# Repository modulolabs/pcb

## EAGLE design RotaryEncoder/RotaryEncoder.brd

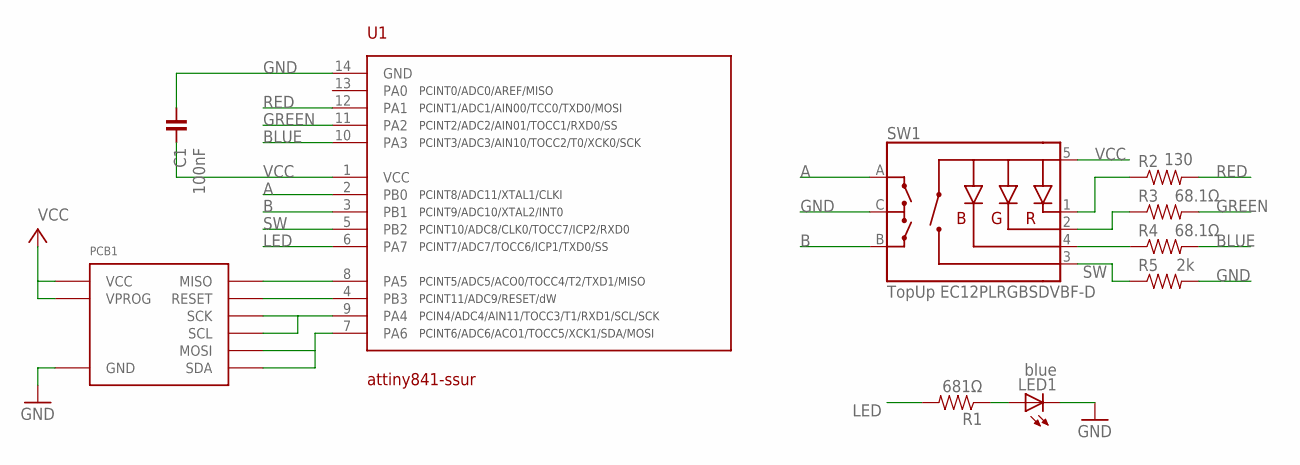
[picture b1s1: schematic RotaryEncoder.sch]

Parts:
C1: 100nF; 0603
LED1: blue; 0805-LED
PCB1: DEVICE-PCB-TABS
R1: 681Ω; 0603
R2: 130; 0603
R3, R4: 68.1Ω; 0603
R5: 2k; 0603
SW1: TopUp EC12PLRGBSDVBF-D; ENCODER_LED_3
U1: attiny841-ssur; SOIC14

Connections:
A: SW1.A, U1.2 (PB0)
B: SW1.B, U1.3 (PB1)
BLUE: R4.2, U1.10 (PA3)
GND: C1.2, LED1.C, PCB1.BUS0 (GND), R5.2, SW1.C, U1.14 (GND)
GREEN: R3.2, U1.11 (PA2)
LED: R1.2, U1.6 (PA7)
MISO: PCB1.PROG3 (MISO), U1.8 (PA5)
unnamed: R2.1, SW1.1 (-R)
unnamed: R3.1, SW1.2 (-G)
unnamed: R4.1, SW1.4 (-B)
unnamed: LED1.A, R1.1
RED: R2.2, U1.12 (PA1)
RESET: PCB1.PROG1 (RESET), U1.4 (PB3)
SCL/SCK: PCB1.BUS3 (SCL), PCB1.PROG2 (SCK), U1.9 (PA4)
SDA/MOSI: PCB1.BUS1 (SDA), PCB1.PROG4 (MOSI), U1.7 (PA6)
SW: R5.1, SW1.3 (SW), U1.5 (PB2)
VCC: C1.1, PCB1.BUS2 (VCC), PCB1.PROG0 (VPROG), SW1.5 (+), U1.1 (VCC)

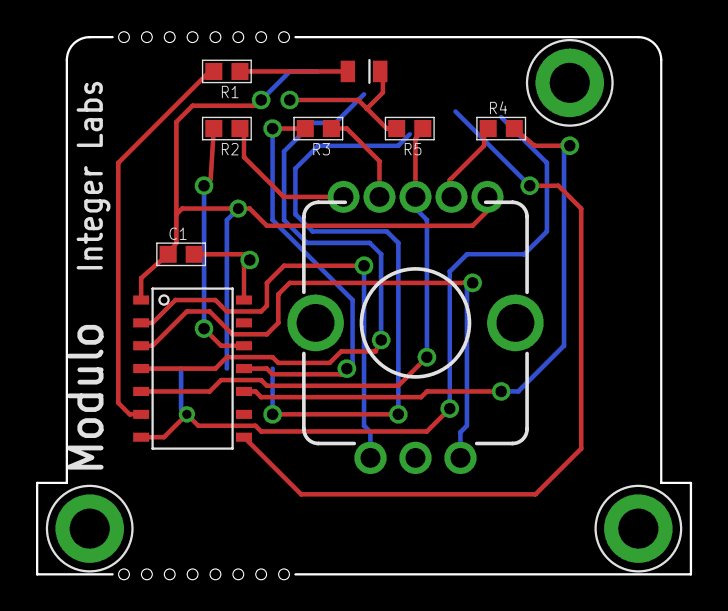
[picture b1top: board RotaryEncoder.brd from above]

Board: 2 copper layers, 10 parts (0 on the bottom side), 17 nets.

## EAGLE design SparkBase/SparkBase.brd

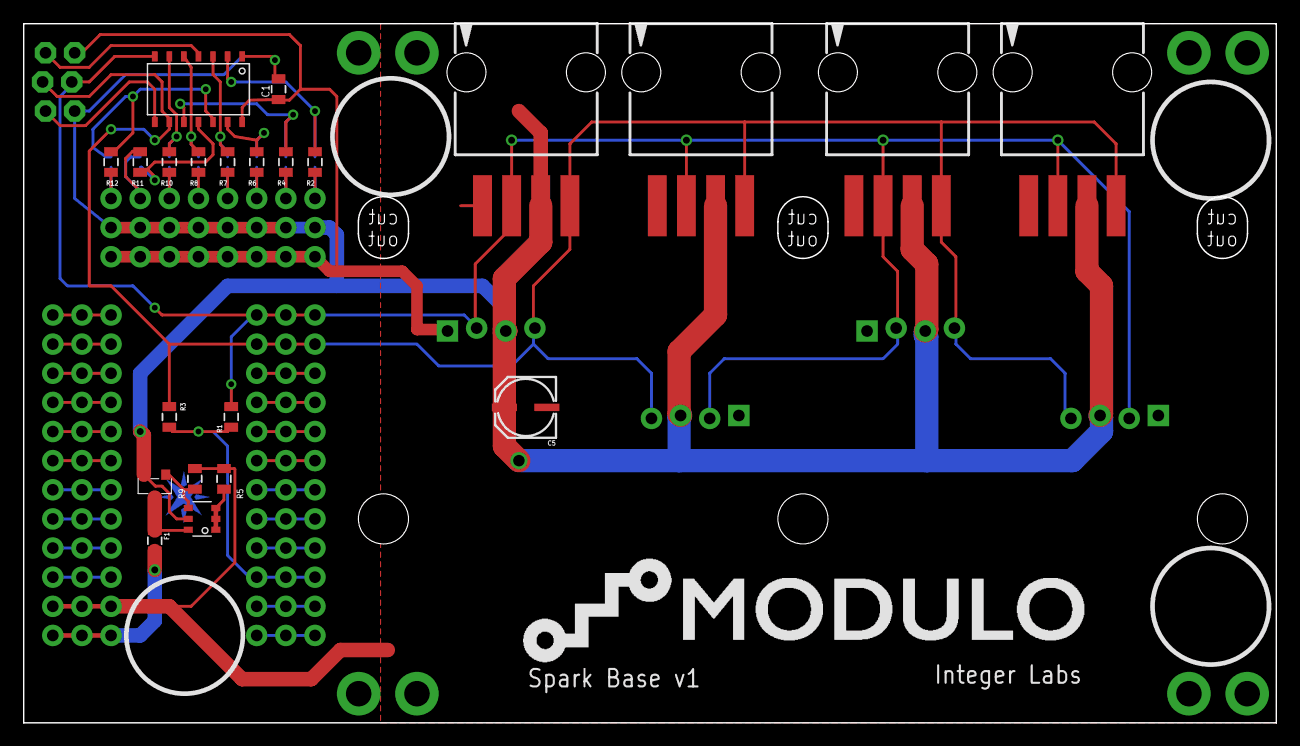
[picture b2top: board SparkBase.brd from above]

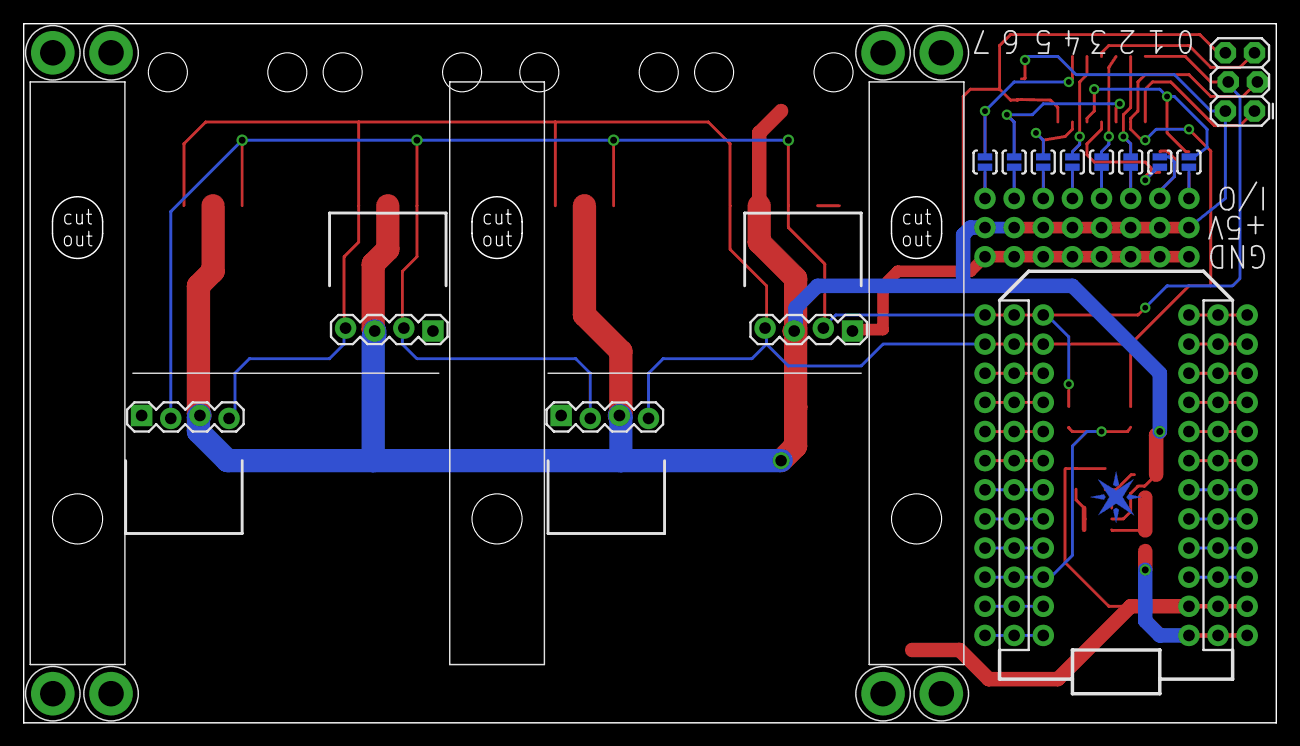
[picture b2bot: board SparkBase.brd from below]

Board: 2 copper layers, 109.2 x 61.0 mm, 52 parts (29 on the bottom side), 46 nets.

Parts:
C1: 0805
C5: PANASONIC_C
F1: 0805
J1: AVR_SPI_PRG_62X3_LOCK; 2X3_LOCK
JP1, JP4, JP11, JP14: 1X04_LOCK
JP2, JP3, JP5: 1X08_NO_SILK
Q2: DMMT5401; SOT-26
Q3: DMG2305UX; MICRO3
R1, R3: 1k; 0805
R2, R4, R6, R7, R8, R10, R11, R12: 130; 0805
R5: 10k 1%; 0805
R9: 47k 1%; 0805
SJ1, SJ2, SJ3, SJ4, SJ5, SJ6, SJ7, SJ8: SOLDERJUMPERNO; SJ_2S-NO
U$1: SPARK_LOGO_PLUS_PLANE
U$2: SPARK_CORE; SPARK_CORE_STACKABLE
U$3, U$4, U$5: CARD-GUIDE-2"
U$6: TINY841; SOIC14
U$7, U$8, U$9, U$10, U$11, U$12, U$13, U$14: HOLE#2; HOLE-#2
U$15: LOGO_WITH_TEXT_0.5
X2, X3, X4, X5: C-GRID-04-15-91; 15-91-04

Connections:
3.3V: R1.1, R3.1, U$2.22, U$2.#22, U$2.@22
GND: C1.1, C5.-, J1.6, JP1.1, JP3.1, JP3.2, JP3.3, JP3.4, JP3.5, JP3.6, JP3.7, JP3.8, JP4.1, JP11.1, JP14.1, R5.1, R9.1, U$2.2, U$2.#2, U$2.@2, U$6.14, X2.1, X3.1, X4.1, X5.1
GPIO0: R12.1, SJ1.2, U$6.12
GPIO1: R11.1, SJ2.2, U$6.11
GPIO2: R10.1, SJ3.2, U$6.6
GPIO3: R8.1, SJ4.2, U$6.5
GPIO4: R7.1, SJ5.2, U$6.3
GPIO5: R6.1, SJ6.2, U$6.13
GPIO6: R4.1, SJ7.2, U$6.10
GPIO7: R2.1, SJ8.2, U$6.2
MISO: J1.1, U$6.8
unnamed: U$2.3, U$2.#3, U$2.@3
unnamed: U$2.4, U$2.#4, U$2.@4
unnamed: U$2.5, U$2.#5, U$2.@5
unnamed: U$2.6, U$2.#6, U$2.@6
unnamed: U$2.7, U$2.#7, U$2.@7
unnamed: U$2.8, U$2.#8, U$2.@8
unnamed: U$2.9, U$2.#9, U$2.@9
unnamed: U$2.10, U$2.#10, U$2.@10
unnamed: U$2.11, U$2.#11, U$2.@11
unnamed: U$2.12, U$2.#12, U$2.@12
unnamed: U$2.24, U$2.#24, U$2.@24
unnamed: U$2.23, U$2.#23, U$2.@23
unnamed: U$2.21, U$2.#21, U$2.@21
unnamed: Q2.1, Q2.2, Q2.3, R5.2
unnamed: U$2.20, U$2.#20, U$2.@20
unnamed: Q2.4, Q3.1, R9.2
unnamed: U$2.19, U$2.#19, U$2.@19
unnamed: U$2.18, U$2.#18, U$2.@18
unnamed: U$2.17, U$2.#17, U$2.@17
unnamed: U$2.16, U$2.#16, U$2.@16
unnamed: U$2.15, U$2.#15, U$2.@15
unnamed: JP5.1, R12.2, SJ1.1
unnamed: JP5.2, R11.2, SJ2.1
unnamed: JP5.3, R10.2, SJ3.1
unnamed: JP5.4, R8.2, SJ4.1
unnamed: JP5.5, R7.2, SJ5.1
unnamed: JP5.6, R6.2, SJ6.1
unnamed: JP5.7, R4.2, SJ7.1
unnamed: JP5.8, R2.2, SJ8.1
RESET: J1.5, U$6.4
SCL: J1.3, JP1.4, JP4.4, JP11.4, JP14.4, R3.2, U$2.14, U$2.#14, U$2.@14, U$6.9, X2.4, X3.4, X4.4, X5.4
SDA: J1.4, JP1.2, JP4.2, JP11.2, JP14.2, R1.2, U$2.13, U$2.#13, U$2.@13, U$6.7, X2.2, X3.2, X4.2, X5.2
VCC: C1.2, C5.+, J1.2, JP1.3, JP2.1, JP2.2, JP2.3, JP2.4, JP2.5, JP2.6, JP2.7, JP2.8, JP4.3, JP11.3, JP14.3, Q2.5, Q3.2, U$6.1, X2.3, X3.3, X4.3, X5.3
VIN: F1.2, U$2.1, U$2.#1, U$2.@1
VREG: F1.1, Q2.6, Q3.3

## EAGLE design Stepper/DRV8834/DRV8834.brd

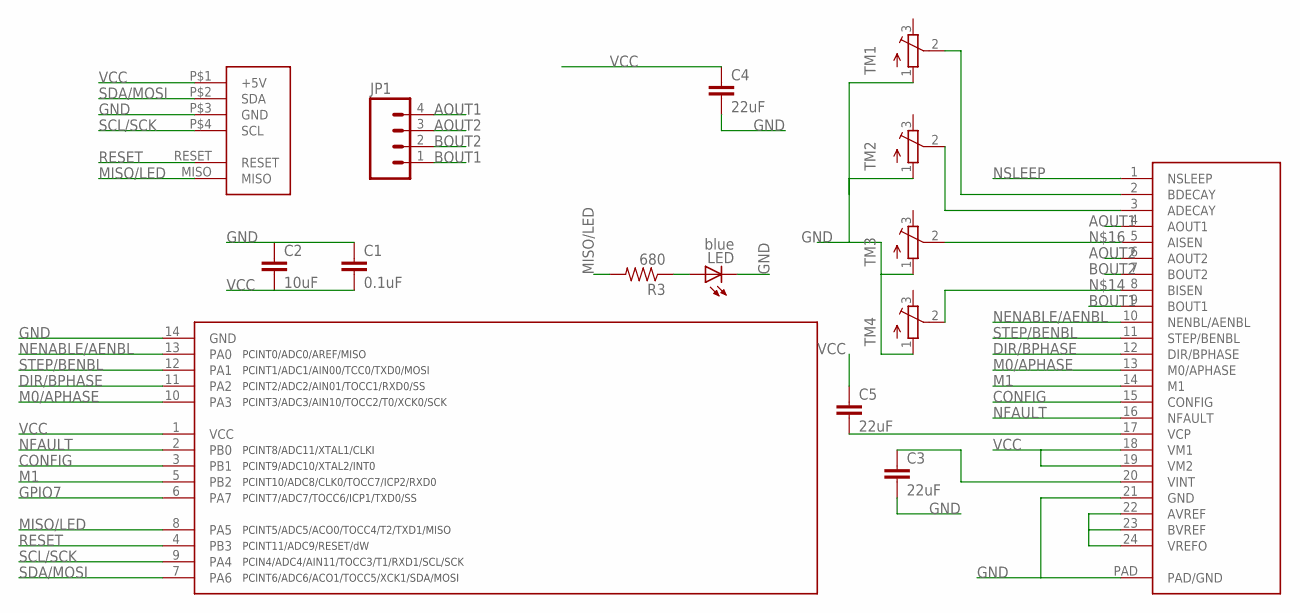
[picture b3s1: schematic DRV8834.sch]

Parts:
C1: 0.1uF; 0805
C2: 10uF; 0805
C3, C4, C5: 22uF; 0805
JP1: M04SCREW_LOCK; SCREWTERMINAL-3.5MM-4_LOCK
LED: blue; CHIPLED_1206
R3: 680; 0805
TM1, TM2, TM3, TM4: TRIMPOTTC33X; TC33X
U$1: DRV8834; HTSSOP-24
U$3: TINY841; SOIC14
U$4: FOOTPRINT

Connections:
AOUT1: JP1.4, U$1.4 (AOUT1)
AOUT2: JP1.3, U$1.6 (AOUT2)
BOUT1: JP1.1, U$1.9 (BOUT1)
BOUT2: JP1.2, U$1.7 (BOUT2)
CONFIG: U$1.15 (CONFIG), U$3.3 (PB1)
DIR/BPHASE: U$1.12 (DIR/BPHASE), U$3.11 (PA2)
GND: C1.1, C2.1, C3.2, C4.2, LED.C, TM1.1 (A), TM2.1 (A), TM3.1 (A), TM4.1 (A), U$1.21 (GND), U$1.PAD (PAD/GND), U$3.14 (GND), U$4.P$3 (GND)
GPIO7: U$3.6 (PA7)
M0/APHASE: U$1.13 (M0/APHASE), U$3.10 (PA3)
M1: U$1.14 (M1), U$3.5 (PB2)
MISO/LED: R3.2, U$3.8 (PA5), U$4.MISO
unnamed: LED.A, R3.1
unnamed: C5.2, U$1.17 (VCP)
unnamed: TM1.2 (S), U$1.2 (BDECAY)
unnamed: TM2.2 (S), U$1.3 (ADECAY)
unnamed: C3.1, U$1.20 (VINT)
unnamed: U$1.22 (AVREF), U$1.23 (BVREF), U$1.24 (VREFO)
unnamed: TM4.2 (S), U$1.8 (BISEN)
unnamed: TM3.2 (S), U$1.5 (AISEN)
NENABLE/AENBL: U$1.10 (NENBL/AENBL), U$3.13 (PA0)
NFAULT: U$1.16 (NFAULT), U$3.2 (PB0)
NSLEEP: U$1.1 (NSLEEP)
RESET: U$3.4 (PB3), U$4.RESET
SCL/SCK: U$3.9 (PA4), U$4.P$4 (SCL)
SDA/MOSI: U$3.7 (PA6), U$4.P$2 (SDA)
STEP/BENBL: U$1.11 (STEP/BENBL), U$3.12 (PA1)
VCC: C1.2, C2.2, C4.1, C5.1, U$1.18 (VM1), U$1.19 (VM2), U$3.1 (VCC), U$4.P$1 (+5V)

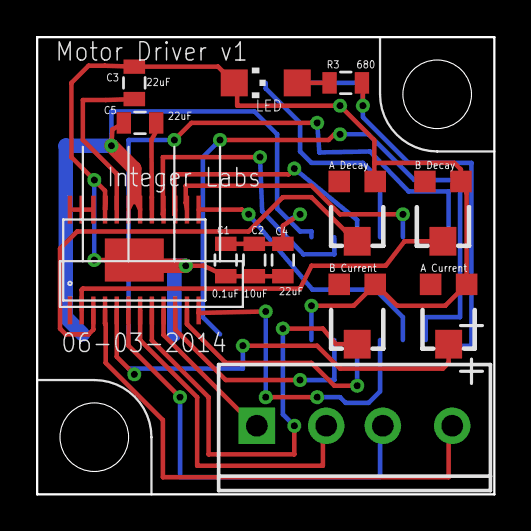
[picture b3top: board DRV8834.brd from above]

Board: 2 copper layers, 25.4 x 25.4 mm, 15 parts (1 on the bottom side), 25 nets.

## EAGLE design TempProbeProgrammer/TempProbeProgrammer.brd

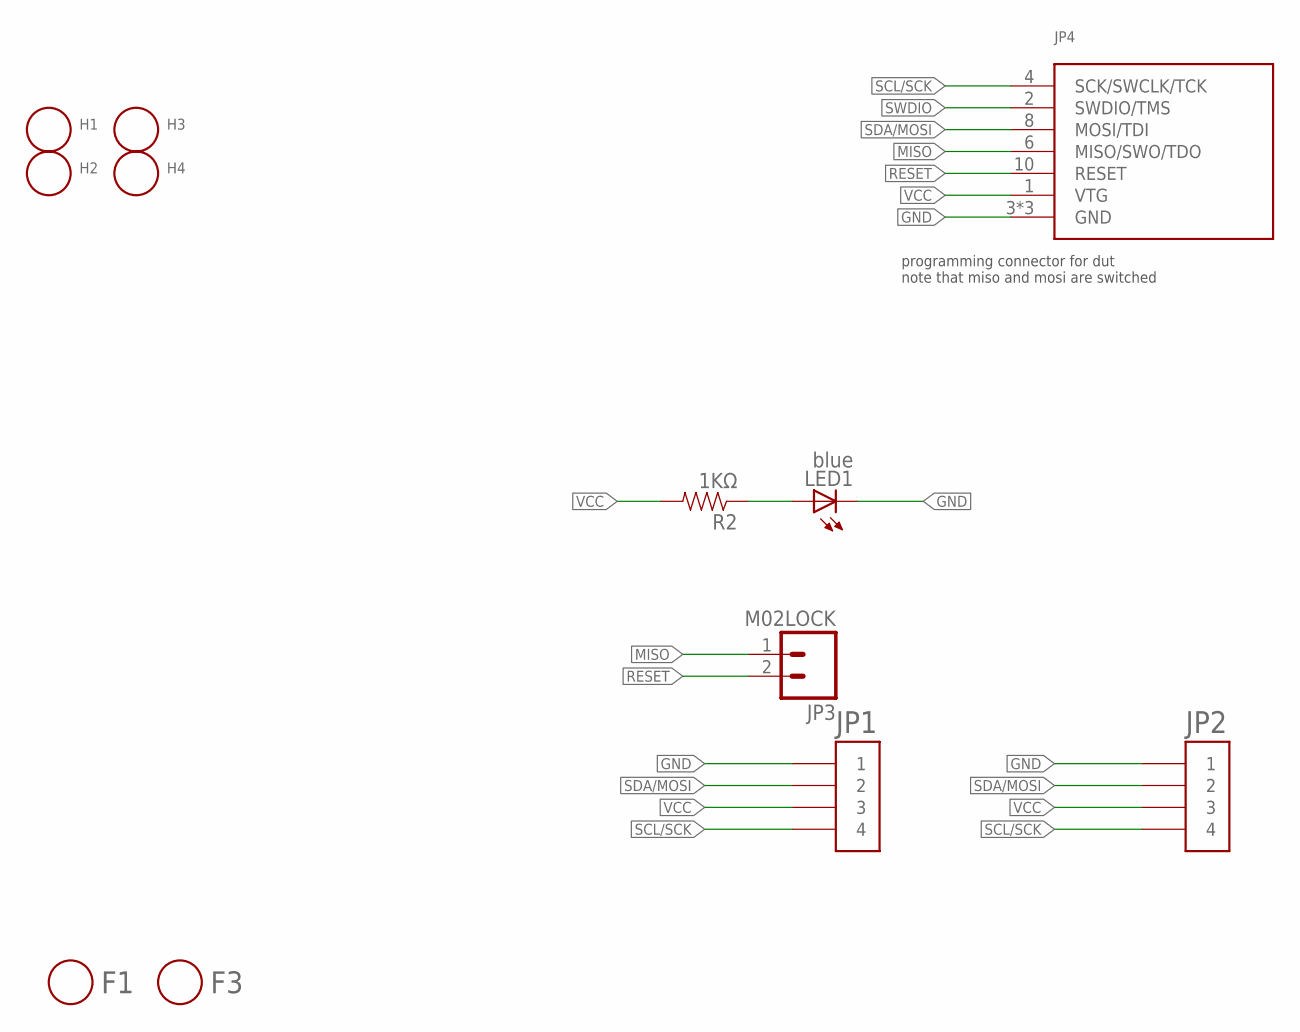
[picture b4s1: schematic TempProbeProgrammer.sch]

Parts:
F1, F3: FIDUCIAL; FIDUCIAL_1MM
H1, H2, H3, H4: HOLE#4; HOLE-#4
JP1, JP2: HEADER-1X4-JST-PA-SIDE-SMD; JST-PA-SIDE-SMD
JP3: M02LOCK; 1X02_LOCK; PARTNUM EXCLUDE
JP4: ICSP; 2X5-.05
LED1: blue; 0805-LED
R2: 1KΩ; 0603

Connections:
GND: JP1.1, JP2.1, JP4.3 (GND), JP4.5 (GND), JP4.9 (GND), LED1.C
MISO: JP3.1, JP4.6 (MISO/SWO/TDO)
unnamed: LED1.A, R2.1
RESET: JP3.2, JP4.10 (RESET)
SCL/SCK: JP1.4, JP2.4, JP4.4 (SCK/SWCLK/TCK)
SDA/MOSI: JP1.2, JP2.2, JP4.8 (MOSI/TDI)
SWDIO: JP4.2 (SWDIO/TMS)
VCC: JP1.3, JP2.3, JP4.1 (VTG), R2.2

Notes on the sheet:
programming connector for dut note that miso and mosi are switched

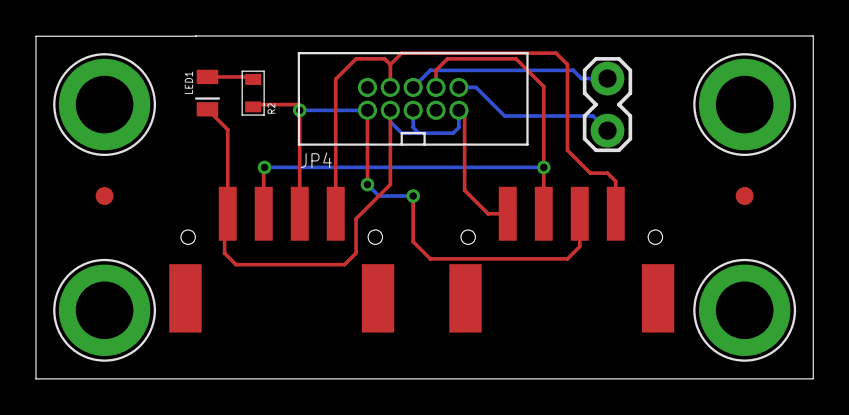
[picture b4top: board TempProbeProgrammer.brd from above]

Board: 2 copper layers, 43.2 x 19.1 mm, 12 parts (0 on the bottom side), 7 nets.

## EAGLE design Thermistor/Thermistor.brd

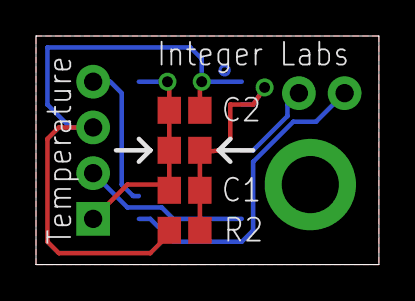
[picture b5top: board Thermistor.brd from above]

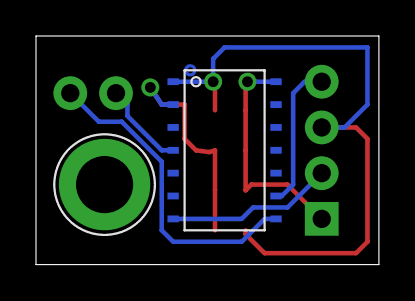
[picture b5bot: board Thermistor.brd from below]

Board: 2 copper layers, 19.1 x 12.7 mm, 8 parts (2 on the bottom side), 7 nets.

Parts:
C1, C2: C0805
JP2: 1X04_NO_SILK
JP4: M021X02_NO_SILK; 1X02_NO_SILK
R1, R2: R0805
U$1: TINY841; SOIC14
U$2: HOLE#4; HOLE-#4

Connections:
GND: C1.1, C2.1, JP2.1, R1.2, U$1.14
MISO: JP4.2, U$1.8
unnamed: C1.2, R1.1, R2.2, U$1.2
RESET: JP4.1, U$1.4
SCL: JP2.4, U$1.9
SDA: JP2.2, U$1.7
VCC: C2.2, JP2.3, R2.1, U$1.1

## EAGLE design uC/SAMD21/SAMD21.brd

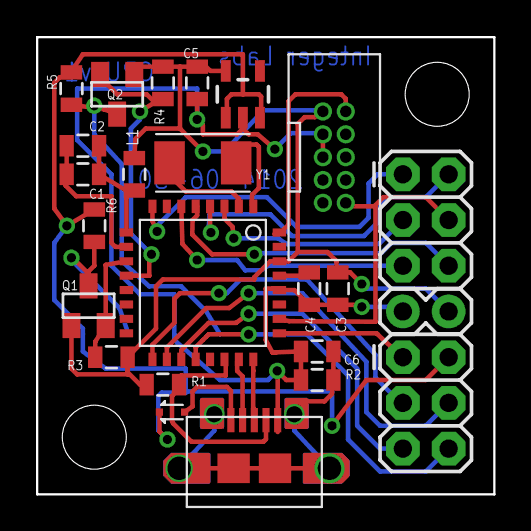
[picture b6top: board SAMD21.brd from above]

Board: 2 copper layers, 25.4 x 25.4 mm, 25 parts (0 on the bottom side), 30 nets.

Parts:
C1, C3, C4: .1uF; 0805
C2, C5: 10uF; 0805
C6: 4.5nF; 0805
D1: DIODE-SCHOTTKY; SOD-523
JP3: M02PTH; 1X02
JP4, JP6: 2X3
L1: 0805
Q1, Q2: BSS138; SOT23
R1: 0805
R2: 1M; 0805
R3, R4, R5, R6: 1k; 0805
U$1: SAMD21E; TQFP-32
U$2: MIC5205-3.3; SOT23-5
U$3: USB-MICRO-AB; MOLEX-MICROAB
U$4: FOOTPRINT
U$5: CORTEX-DEBUG; HEADER-10-.05
Y1: CRYSTAL-TXC-7A

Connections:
+3.3V: C3.1, C5.1, JP3.2, L1.2, Q1.1, Q2.1, R1.1, R3.1, R4.1, U$1.30, U$2.5, U$5.1
+5V: D1.C, JP6.2, R5.2, R6.2, U$2.1, U$2.3, U$4.P$1
A2: JP4.3, U$1.3
A3: JP4.2, U$1.4
A4: JP4.6, U$1.5
A5: JP4.5, U$1.6
A7: JP4.1, U$1.8
A16: JP6.3, U$1.17
A17: JP6.4, U$1.18
A18: JP6.5, U$1.19
A19: JP6.6, U$1.20
A27: JP6.1, U$1.25
D+: U$1.24, U$3.3
D-: U$1.23, U$3.2
GND: C3.2, C4.2, C5.2, C6.2, JP3.1, R2.1, U$1.28, U$2.2, U$3.5, U$4.P$3, U$5.2, U$5.3
unnamed: C1.1, C2.1, L1.1, U$1.9
unnamed: C1.2, C2.2, U$1.10
unnamed: C6.1, R2.2, U$3.S1, U$3.S2, U$3.S3, U$3.S4, U$3.S5, U$3.S6
unnamed: D1.A, U$3.1
unnamed: C4.1, U$1.29
unnamed: U$1.1, Y1.P$2
unnamed: U$1.2, Y1.P$1
RESETN: JP4.4, U$1.26, U$5.6
SCL: Q2.3, R5.1, U$4.P$4
SCL3.3: Q2.2, R4.2, U$1.12
SDA: Q1.3, R6.1, U$4.P$2
SDA3.3: Q1.2, R3.2, U$1.11
SWDCLK: U$1.31, U$5.9
SWDIO: U$1.32, U$5.10
USB-ID: R1.2, U$1.22, U$3.4

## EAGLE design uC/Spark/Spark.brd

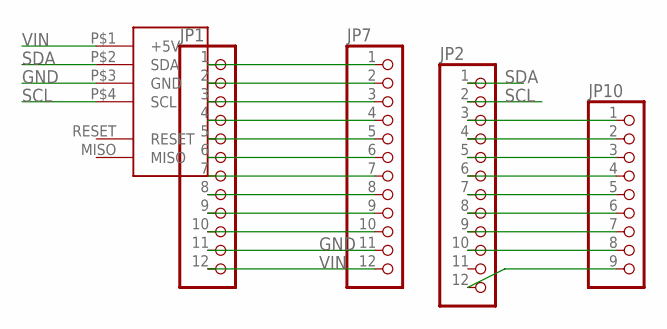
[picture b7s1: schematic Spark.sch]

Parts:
JP1, JP2, JP7: PINHD-1X12-CB; 1X12-CB
JP10: PINHD-1X9; 1X09-BIG
U$1: FOOTPRINTDOUBLE; FOOTPRINT-DOUBLE

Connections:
GND: JP1.2, JP7.2, U$1.P$3 (GND)
unnamed: JP2.3, JP10.1
unnamed: JP2.4, JP10.2
unnamed: JP2.5, JP10.3
unnamed: JP2.6, JP10.4
unnamed: JP2.7, JP10.5
unnamed: JP2.8, JP10.6
unnamed: JP2.9, JP10.7
unnamed: JP2.10, JP10.8
unnamed: JP2.12, JP10.9
unnamed: JP1.3, JP7.3
unnamed: JP1.4, JP7.4
unnamed: JP1.5, JP7.5
unnamed: JP1.6, JP7.6
unnamed: JP1.7, JP7.7
unnamed: JP1.8, JP7.8
unnamed: JP1.9, JP7.9
unnamed: JP1.10, JP7.10
unnamed: JP1.11, JP7.11
unnamed: JP1.12, JP7.12
SCL: JP2.2, U$1.P$4 (SCL)
SDA: JP2.1, U$1.P$2 (SDA)
VIN: JP1.1, JP7.1, U$1.P$1 (+5V)

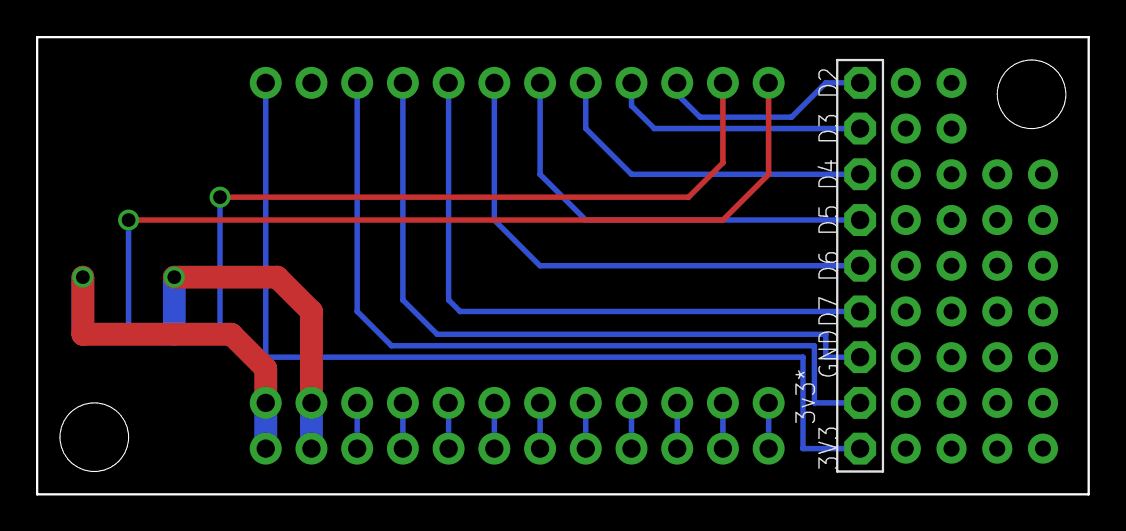
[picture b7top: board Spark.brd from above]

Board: 2 copper layers, 58.4 x 25.4 mm, 5 parts (0 on the bottom side), 23 nets.

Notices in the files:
parts and their libraries:
SparkFun-Electromechanical: Licensing: Creative Commons ShareAlike 4.0 International - https://creativecommons.org/licenses/by-sa/4.0
